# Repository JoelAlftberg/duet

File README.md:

# duet
A devboard featuring a Lattice ECP5 FPGA and an Espressif ESP32-S3

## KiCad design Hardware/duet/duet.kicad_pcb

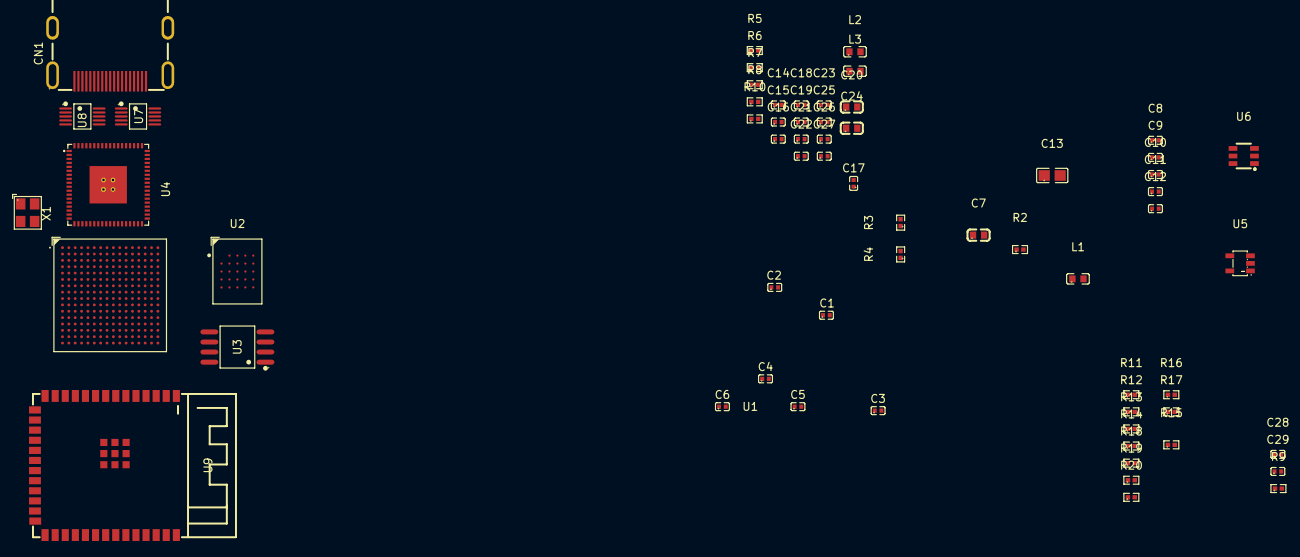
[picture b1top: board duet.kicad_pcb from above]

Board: 2 copper layers, 62 parts (0 on the bottom side), 79 nets, no tracks yet.

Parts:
C1, C2, C3, C4, C5, C6, C9, C10, C11, C14, C15, C16, C17, C18, C19, C21, C22, C23, C25, C26, C27, C28: 100 nF; C0402
C7, C20, C24: 10 uF; C0603
C8, C12: 10 nF; C0402
C13: 22 uF; C0805
C29: CL05B104KO5NNNC; C0402
CN1: A71-05H5-111N1; HDMI-SMD_A71-05H5-111N1
L1, L2, L3: 600ohm@100MHz; L0603
R2, R9, R15, R16, R17: 10k; R0402
R3, R4: 2.2k; R0402
R5, R6, R10, R11, R12, R13, R14, R18, R19, R20: 4.7k; R0402
R7: 100 Ohm; R0402
R8: 4.3k; R0402
U1: LFE5U-45F-6BG256C; CABGA-256_L14.0-W14.0-R16-C16-P0.80-TL
U2: W956D8MBYA5I; BGA-24_L8.0-W6.0-W5-R5-P1.00-TL
U3: W25Q128JVSIQTR; SOIC-8_L5.3-W5.3-P1.27-LS8.0-BL
U4: SII9022ACNU; QFN-72_L10.0-W10.0-P0.50-BL-EP
U5: RT9013-12GB; SOT-23-5_L3.0-W1.7-P0.95-LS2.8-BR
U6: TPS563201DDCR; SOT-23-6_L2.9-W1.6-P0.95-LS2.8-BR
U7, U8: RCLAMP0514M; MSOP-10_L3.0-W3.0-P0.50-LS5.0-BL
U9: ESP32-S3-WROOM-1; WIRELM-SMD_ESP32-S3-WROOM-1
X1: OT322525MJBA4SL; OSC-SMD_4P-L3.2-W2.5-BL

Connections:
+1V1: C1.2, C2.2, C3.2, C4.2, C5.2, C6.2, U1.G6 (VCC), U1.G7 (VCC), U1.G9 (VCC), U1.L8 (VCC), U1.L9 (VCC), U1.L10 (VCC)
+1V2: C13.1, C20.1, L1.2, L2.2
+1V8: U1.H11 (VCCIO2), U1.J11 (VCCIO2), U2.B4 (VCC), U2.D1 (VCCQ), U2.E4 (VCCQ)
+3.3V: C24.1, C26.1, C27.1, C28.1, R5.2, R6.2, R9.2, R10.2, R12.2, R13.2, R14.2, R15.2, R16.2, R17.2, R18.2, R19.2, R20.2, U1.L6 (VCCIO8), U3.8 (VCC), U7.3 (VCC), U8.3 (VCC), U9.2 (3V3), X1.4 (VDD)
+5V: R3.2, R4.2, R7.1
/ESP32/ESP_EN: C29.1, R9.1, U9.3 (EN)
/FPGA/FPGA-PCLK: U1.A8 (PT38B/PCLKC0_0), X1.3 (OUT)
/HDMI/+1V2_AVCC: C7.1, C8.1, C9.1, C10.1, C11.1, C12.1, L1.1, U4.60 (AVCC12), U4.66 (AVCC12)
/HDMI/+1V2_CVCC: C14.1, C15.1, C16.1, C17.1, C18.1, C19.1, L2.1, U4.5 (CVCC12), U4.12 (CVCC12), U4.26 (CVCC12), U4.42 (CVCC12), U4.47 (CVCC12), U4.53 (CVCC12)
/HDMI/+3.3V_IOVCC: C21.1, C22.1, C23.1, L3.1 (1_1), U4.3 (IOVCC), U4.21 (IOVCC), U4.46 (IOVCC)
/HDMI/+5V_HDMI: C25.1, CN1.18 (+5VPower), R7.2
/HDMI/CEC_A: CN1.13 (CEC), U4.71 (CEC_A)
/HDMI/DSCL: CN1.15 (SCL), R3.1, U4.49 (DSCL)
/HDMI/DSDA: CN1.16 (SDA), R4.1, U4.48 (DSDA)
/HDMI/EXT_SWING: R8.1, U4.56 (EXT_SWING)
/HDMI/HPD: CN1.19 (HotPlugDetect), R2.1, U4.54 (HPD)
/HDMI/TX0+: CN1.7 (TMDSData0+), U4.62 (TX0+), U7.1 (LINE1)
/HDMI/TX0-: CN1.9 (TMDSData0-), U4.61 (TX0-), U7.4 (LINE3)
/HDMI/TX1+: CN1.4 (TMDSData1+), U4.65 (TX1+), U8.9 (LINE2)
/HDMI/TX1-: CN1.6 (TMDSData1-), U4.64 (TX1-), U8.6 (LINE4)
/HDMI/TX2+: CN1.1 (TMDSData2+), U4.68 (TX2+), U8.1 (LINE1)
/HDMI/TX2-: CN1.3 (TMDSData2-), U4.67 (TX2-), U8.4 (LINE3)
/HDMI/TXC+: CN1.10 (TMDSClock+), U4.59 (TXC+), U7.9 (LINE2)
/HDMI/TXC-: CN1.12 (TMDSClock-), U4.58 (TXC-), U7.6 (LINE4)
CI2CA: R10.1, U4.72 (CI2CA)
CK: U1.F16 (PR23A), U2.B2 (CK)
CSCL: R5.1, U4.1 (CSCL)
CSDA: R6.1, U4.2 (CSDA)
D0: U1.C8 (PT44A/PCLKT1_0), U4.32 (D0)
D1: U1.D8 (PT42B/PCLKC1_1), U4.31 (D1)
D2: U1.B8 (PT44B/PCLKC1_0), U4.30 (D2)
D3: U1.B9 (PT47A/GR_PCLK1_0), U4.29 (D3)
D4: U1.D9 (PT49A), U4.28 (D4)
D5: U1.C9 (PT47B/GR_PCLK1_1), U4.27 (D5)
D6: U1.E9 (PT49B), U4.25 (D6)
D7: U1.A9 (PT51A), U4.24 (D7)
D8: U1.B10 (PT53A), U4.23 (D8)
D9: U1.A10 (PT51B), U4.20 (D9)
D10: U1.C10 (PT53B), U4.19 (D10)
D11: U1.D10 (PT56A), U4.18 (D11)
D12: U1.B11 (PT58A), U4.17 (D12)
D13: U1.E10 (PT56B), U4.16 (D13)
D14: U1.C11 (PT58B), U4.15 (D14)
D15: U1.D11 (PT69A), U4.14 (D15)
D16: U1.A11 (PT71A), U4.13 (D16)
D17: U1.E11 (PT69B), U4.11 (D17)
D18: U1.A12 (PT71B), U4.10 (D18)
D19: U1.B12 (PT74A), U4.9 (D19)
D20: U1.D12 (PT76A), U4.8 (D20)
D21: U1.C12 (PT74B), U4.7 (D21)
D22: U1.E12 (PT76B), U4.6 (D22)
D23: U1.B13 (PT78A), U4.4 (D23)
DQ0: U1.B16 (PR11A/URC_GPLL0T_IN), U2.D3 (DQ0)
DQ1: U1.B15 (PR11B/URC_GPLL0C_IN), U2.D2 (DQ1)
DQ2: U1.C16 (PR14A), U2.C4 (DQ2)
DQ3: U1.C15 (PR14B), U2.D4 (DQ3)
DQ4: U1.D16 (PR17A), U2.D5 (DQ4)
DQ5: U1.E15 (PR17B), U2.E3 (DQ5)
DQ6: U1.G12 (PR20A), U2.E2 (DQ6)
DQ7: U1.G13 (PR20B), U2.E1 (DQ7)
FLASH-CLK: R17.1, U1.N9 (CCLK/MCLK/SCK), U3.6 (CLK)
FLASH-IO0: U1.T8 (PB11B/D0/MOSI/IO0), U3.5 (DI)
FLASH-IO1: U1.T7 (PB11A/D1/MISO/IO1), U3.2 (DO)
FLASH-IO2: U1.M7 (PB9B/D2/IO2), U3.3 (IO2)
FLASH-IO3: U1.N7 (PB9A/D3/IO3), U3.7 (IO3)
FLASH-~CS: R16.1, U1.N8 (PB15A/HOLDN/DI/BUSY/CSSPIN/CEN), U3.1 (~CS)
FPGA-DONE: R20.1, U1.P9 (DONE), U9.8 (IO15)
FPGA-INITN: R19.1, U1.T9 (INITN), U9.9 (IO16)
FPGA-PROGRAMN: R18.1, U1.R9 (PROGRAMN), U9.10 (IO17)
FPGA-TCK: R11.1, U1.T10 (TCK), U9.4 (IO4)
FPGA-TDI: R12.1, U1.R11 (TDI), U9.5 (IO5)
FPGA-TDO: R14.1, U1.M10 (TDO), U9.7 (IO7)
FPGA-TMS: R13.1, U1.T11 (TMS), U9.6 (IO6)
GND: C1.1, C2.1, C3.1, C4.1, C5.1, C6.1, C7.2, C8.2, C9.2, C10.2, C11.2, C12.2, C13.2, C14.2, C15.2, C16.2, C17.2, C18.2, C19.2, C20.2, C21.2, C22.2, C23.2, C24.2, C25.2, C26.2, C27.2, C28.2, C29.2, CN1.2 (TMDSData2Shield), CN1.5 (TMDSData1Shield), CN1.8 (TMDSData0Shield), CN1.11 (TMDSClockShield), CN1.17 (DDC/CECGround), CN1.20 (EH), CN1.21 (EH), CN1.22 (EH), CN1.23 (EH), R2.2, R8.2, R11.2, U1.A1 (GND), U1.A16 (GND), U1.D2 (GND), U1.D15 (GND), U1.F8 (GND), U1.F9 (GND), U1.G8 (GND), U1.G10 (GND), U1.H1 (GND), U1.H8 (GND), U1.H9 (GND), U1.H10 (GND), U1.H16 (GND), U1.J8 (GND), U1.J9 (GND), U1.J10 (GND), U1.K6 (GND), U1.K7 (GND), U1.K8 (GND), U1.K9 (GND), U1.K10 (GND), U1.N2 (GND), U1.N10 (CFG_0), U1.N15 (GND), U1.R10 (CFG_2), U1.T1 (GND), U1.T5 (GND), U1.T12 (GND), U1.T16 (GND), U2.B3 (VSS), U2.C1 (VSSQ), U2.E5 (VSSQ), U3.4 (GND), U4.43 (CGND), U4.55 (RSVDL), U4.57 (IOGND), U4.63 (AGND), U4.69 (IO_SEL), U4.70 (VDDQ), U4.73 (EP), U7.8 (GND), U8.8 (GND), U9.1 (GND), U9.40 (GND), U9.41 (GND), X1.2 (GND)
IDCK: U1.E8 (PT42A/PCLKT1_1), U4.22 (IDCK)
unnamed: R15.1, U1.P10 (CFG_1)
~CK: U1.G15 (PR23B), U2.B1 (~CK)
~CS: U1.G14 (PR23C/VREF1_2), U2.A3 (~CS)
~RESET: U1.E16 (PR20D), U2.A4 (~RESET)

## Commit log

2026-05-08 Add kicad proj base and md notes
2026-05-09 Add RAM to kicad schematic
2026-05-10 Add ECP5 configuration pins and labels
2026-05-10 Adds HDMI transmitter and connector
2026-05-11 Adds ESP32 and pull up-down resistors
2026-05-13 Add mezzanine connector and finalze HDMI
